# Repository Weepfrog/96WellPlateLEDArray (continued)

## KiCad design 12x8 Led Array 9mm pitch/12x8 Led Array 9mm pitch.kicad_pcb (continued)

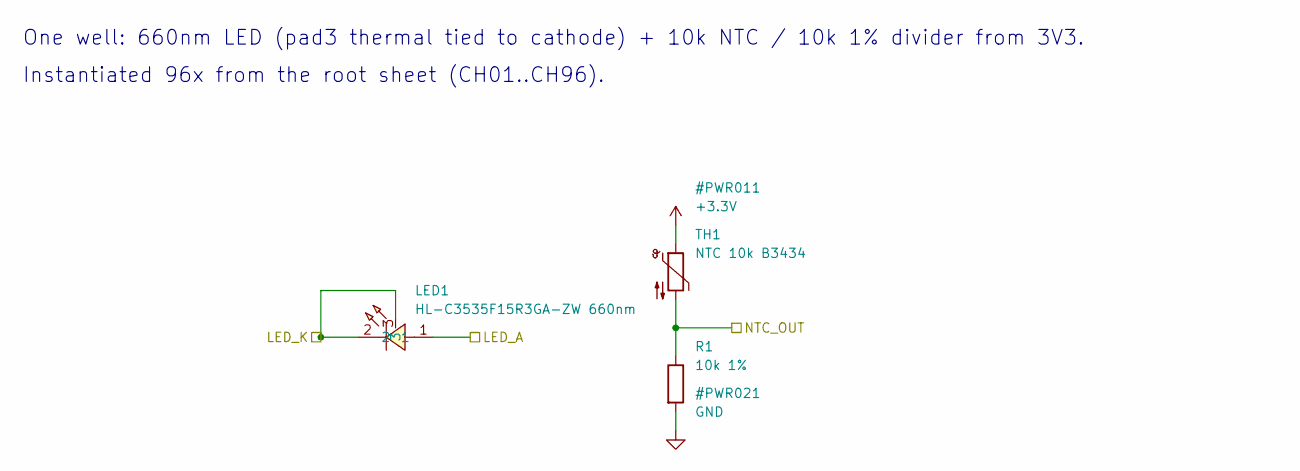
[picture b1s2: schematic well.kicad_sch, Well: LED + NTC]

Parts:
LED1: HL-C3535F15R3GA-ZW 660nm; LED-SMD_3P-L3.5-W3.5_NLW3535AV2; LCSC C5445086
R1: 10k 1%; R_0603_1608Metric; LCSC C25804
TH1: NTC 10k B3434; R_0603_1608Metric; LCSC C13564

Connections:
+3.3V: TH1.1; also elsewhere on the board
/LED_A14: LED1.1; also elsewhere on the board
/LED_K14: LED1.2, LED1.3; also elsewhere on the board
/NTC1: R1.1, TH1.2; also elsewhere on the board
GND: R1.2; also elsewhere on the board

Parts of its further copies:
LED2, LED3, LED4, LED5, LED6, LED7, LED8, LED9, LED10, LED11, LED12, LED13, LED14, LED15, LED16, LED17, LED18, LED19, LED20, LED21, LED22, LED23, LED24, LED25, LED26, LED27, LED28, LED29, LED30, LED31, LED32, LED33, LED34, LED35, LED36, LED37, LED38, LED39, LED40, LED41, LED42, LED43, LED44, LED45, LED46, LED47, LED48, LED49, LED50, LED51, LED52, LED53, LED54, LED55, LED56, LED57, LED58, LED59, LED60, LED61, LED62, LED63, LED64, LED65, LED66, LED67, LED68, LED69, LED70, LED71, LED72, LED73, LED74, LED75, LED76, LED77, LED78, LED79, LED80, LED81, LED82, LED83, LED84, LED85, LED86, LED87, LED88, LED89, LED90, LED91, LED92, LED93, LED94, LED95, LED96: HL-C3535F15R3GA-ZW 660nm; LED-SMD_3P-L3.5-W3.5_NLW3535AV2; LCSC C5445086
R2, R3, R4, R5, R6, R7, R8, R9, R10, R11, R12, R13, R14, R15, R16, R17, R18, R19, R20, R21, R22, R23, R24, R25, R26, R27, R28, R29, R30, R31, R32, R33, R34, R35, R36, R37, R38, R39, R40, R41, R42, R43, R44, R45, R46, R47, R48, R49, R50, R51, R52, R53, R54, R55, R56, R57, R58, R59, R60, R61, R62, R63, R64, R65, R66, R67, R68, R69, R70, R71, R72, R73, R74, R75, R76, R77, R78, R79, R80, R81, R82, R83, R84, R85, R86, R87, R88, R89, R90, R91, R92, R93, R94, R95, R96: 10k 1%; R_0603_1608Metric; LCSC C25804
TH2, TH3, TH4, TH5, TH6, TH7, TH8, TH9, TH10, TH11, TH12, TH13, TH14, TH15, TH16, TH17, TH18, TH19, TH20, TH21, TH22, TH23, TH24, TH25, TH26, TH27, TH28, TH29, TH30, TH31, TH32, TH33, TH34, TH35, TH36, TH37, TH38, TH39, TH40, TH41, TH42, TH43, TH44, TH45, TH46, TH47, TH48, TH49, TH50, TH51, TH52, TH53, TH54, TH55, TH56, TH57, TH58, TH59, TH60, TH61, TH62, TH63, TH64, TH65, TH66, TH67, TH68, TH69, TH70, TH71, TH72, TH73, TH74, TH75, TH76, TH77, TH78, TH79, TH80, TH81, TH82, TH83, TH84, TH85, TH86, TH87, TH88, TH89, TH90, TH91, TH92, TH93, TH94, TH95, TH96: NTC 10k B3434; R_0603_1608Metric; LCSC C13564

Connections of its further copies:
+3.3V: TH2.1, TH3.1, TH4.1, TH5.1, TH6.1, TH7.1, TH8.1, TH9.1, TH10.1, TH11.1, TH12.1, TH13.1, TH14.1, TH15.1, TH16.1, TH17.1, TH18.1, TH19.1, TH20.1, TH21.1, TH22.1, TH23.1, TH24.1, TH25.1, TH26.1, TH27.1, TH28.1, TH29.1, TH30.1, TH31.1, TH32.1, TH33.1, TH34.1, TH35.1, TH36.1, TH37.1, TH38.1, TH39.1, TH40.1, TH41.1, TH42.1, TH43.1, TH44.1, TH45.1, TH46.1, TH47.1, TH48.1, TH49.1, TH50.1, TH51.1, TH52.1, TH53.1, TH54.1, TH55.1, TH56.1, TH57.1, TH58.1, TH59.1, TH60.1, TH61.1, TH62.1, TH63.1, TH64.1, TH65.1, TH66.1, TH67.1, TH68.1, TH69.1, TH70.1, TH71.1, TH72.1, TH73.1, TH74.1, TH75.1, TH76.1, TH77.1, TH78.1, TH79.1, TH80.1, TH81.1, TH82.1, TH83.1, TH84.1, TH85.1, TH86.1, TH87.1, TH88.1, TH89.1, TH90.1, TH91.1, TH92.1, TH93.1, TH94.1, TH95.1, TH96.1; also elsewhere on the board
/LED_A1: LED37.1; also elsewhere on the board
/LED_A2: LED38.1; also elsewhere on the board
/LED_A3: LED39.1; also elsewhere on the board
/LED_A4: LED40.1; also elsewhere on the board
/LED_A5: LED25.1; also elsewhere on the board
/LED_A6: LED41.1; also elsewhere on the board
/LED_A7: LED26.1; also elsewhere on the board
/LED_A8: LED27.1; also elsewhere on the board
/LED_A9: LED13.1; also elsewhere on the board
/LED_A10: LED42.1; also elsewhere on the board
/LED_A11: LED28.1; also elsewhere on the board
/LED_A12: LED14.1; also elsewhere on the board
/LED_A13: LED15.1; also elsewhere on the board
/LED_A15: LED29.1; also elsewhere on the board
/LED_A16: LED2.1; also elsewhere on the board
/LED_A17: LED16.1; also elsewhere on the board
/LED_A18: LED3.1; also elsewhere on the board
/LED_A19: LED43.1; also elsewhere on the board
/LED_A20: LED17.1; also elsewhere on the board
/LED_A21: LED4.1; also elsewhere on the board
/LED_A22: LED30.1; also elsewhere on the board
/LED_A23: LED31.1; also elsewhere on the board
/LED_A24: LED18.1; also elsewhere on the board
/LED_A25: LED5.1; also elsewhere on the board
/LED_A26: LED44.1; also elsewhere on the board
/LED_A27: LED32.1; also elsewhere on the board
/LED_A28: LED6.1; also elsewhere on the board
/LED_A29: LED19.1; also elsewhere on the board
/LED_A30: LED45.1; also elsewhere on the board
/LED_A31: LED7.1; also elsewhere on the board
/LED_A32: LED20.1; also elsewhere on the board
/LED_A33: LED8.1; also elsewhere on the board
/LED_A34: LED33.1; also elsewhere on the board
/LED_A35: LED21.1; also elsewhere on the board
/LED_A36: LED9.1; also elsewhere on the board
/LED_A37: LED46.1; also elsewhere on the board
/LED_A38: LED34.1; also elsewhere on the board
/LED_A39: LED22.1; also elsewhere on the board
/LED_A40: LED10.1; also elsewhere on the board
/LED_A41: LED47.1; also elsewhere on the board
/LED_A42: LED35.1; also elsewhere on the board
/LED_A43: LED23.1; also elsewhere on the board
/LED_A44: LED11.1; also elsewhere on the board
/LED_A45: LED48.1; also elsewhere on the board
/LED_A46: LED36.1; also elsewhere on the board
/LED_A47: LED24.1; also elsewhere on the board
/LED_A48: LED12.1; also elsewhere on the board
/LED_A49: LED65.1; also elsewhere on the board
/LED_A50: LED86.1; also elsewhere on the board
/LED_A51: LED75.1; also elsewhere on the board
/LED_A52: LED85.1; also elsewhere on the board
/LED_A53: LED54.1; also elsewhere on the board
/LED_A54: LED64.1; also elsewhere on the board
/LED_A55: LED74.1; also elsewhere on the board
/LED_A56: LED53.1; also elsewhere on the board
/LED_A57: LED73.1; also elsewhere on the board
/LED_A58: LED63.1; also elsewhere on the board
/LED_A59: LED62.1; also elsewhere on the board
/LED_A60: LED52.1; also elsewhere on the board
/LED_A61: LED61.1; also elsewhere on the board
/LED_A62: LED51.1; also elsewhere on the board
/LED_A63: LED50.1; also elsewhere on the board
/LED_A64: LED49.1; also elsewhere on the board
/LED_A65: LED87.1; also elsewhere on the board
/LED_A66: LED76.1; also elsewhere on the board
/LED_A67: LED55.1; also elsewhere on the board
/LED_A68: LED88.1; also elsewhere on the board
/LED_A69: LED66.1; also elsewhere on the board
/LED_A70: LED77.1; also elsewhere on the board
/LED_A71: LED56.1; also elsewhere on the board
/LED_A72: LED78.1; also elsewhere on the board
/LED_A73: LED89.1; also elsewhere on the board
/LED_A74: LED67.1; also elsewhere on the board
/LED_A75: LED90.1; also elsewhere on the board
/LED_A76: LED79.1; also elsewhere on the board
/LED_A77: LED68.1; also elsewhere on the board
/LED_A78: LED57.1; also elsewhere on the board
/LED_A79: LED91.1; also elsewhere on the board
/LED_A80: LED80.1; also elsewhere on the board
/LED_A81: LED92.1; also elsewhere on the board
/LED_A82: LED69.1; also elsewhere on the board
/LED_A83: LED81.1; also elsewhere on the board
/LED_A84: LED93.1; also elsewhere on the board
/LED_A85: LED58.1; also elsewhere on the board
/LED_A86: LED70.1; also elsewhere on the board
/LED_A87: LED82.1; also elsewhere on the board
/LED_A88: LED94.1; also elsewhere on the board
/LED_A89: LED59.1; also elsewhere on the board
/LED_A90: LED71.1; also elsewhere on the board
/LED_A91: LED83.1; also elsewhere on the board
/LED_A92: LED95.1; also elsewhere on the board
/LED_A93: LED60.1; also elsewhere on the board
/LED_A94: LED72.1; also elsewhere on the board
/LED_A95: LED84.1; also elsewhere on the board
/LED_A96: LED96.1; also elsewhere on the board
/LED_K1: LED37.2, LED37.3; also elsewhere on the board
/LED_K2: LED38.2, LED38.3; also elsewhere on the board
/LED_K3: LED39.2, LED39.3; also elsewhere on the board
/LED_K4: LED40.2, LED40.3; also elsewhere on the board
/LED_K5: LED25.2, LED25.3; also elsewhere on the board
/LED_K6: LED41.2, LED41.3; also elsewhere on the board
/LED_K7: LED26.2, LED26.3; also elsewhere on the board
/LED_K8: LED27.2, LED27.3; also elsewhere on the board
/LED_K9: LED13.2, LED13.3; also elsewhere on the board
/LED_K10: LED42.2, LED42.3; also elsewhere on the board
/LED_K11: LED28.2, LED28.3; also elsewhere on the board
/LED_K12: LED14.2, LED14.3; also elsewhere on the board
/LED_K13: LED15.2, LED15.3; also elsewhere on the board
/LED_K15: LED29.2, LED29.3; also elsewhere on the board
/LED_K16: LED2.2, LED2.3; also elsewhere on the board
/LED_K17: LED16.2, LED16.3; also elsewhere on the board
/LED_K18: LED3.2, LED3.3; also elsewhere on the board
/LED_K19: LED43.2, LED43.3; also elsewhere on the board
/LED_K20: LED17.2, LED17.3; also elsewhere on the board
/LED_K21: LED4.2, LED4.3; also elsewhere on the board
/LED_K22: LED30.2, LED30.3; also elsewhere on the board
/LED_K23: LED31.2, LED31.3; also elsewhere on the board
/LED_K24: LED18.2, LED18.3; also elsewhere on the board
/LED_K25: LED5.2, LED5.3; also elsewhere on the board
/LED_K26: LED44.2, LED44.3; also elsewhere on the board
/LED_K27: LED32.2, LED32.3; also elsewhere on the board
/LED_K28: LED6.2, LED6.3; also elsewhere on the board
/LED_K29: LED19.2, LED19.3; also elsewhere on the board
/LED_K30: LED45.2, LED45.3; also elsewhere on the board
/LED_K31: LED7.2, LED7.3; also elsewhere on the board
/LED_K32: LED20.2, LED20.3; also elsewhere on the board
/LED_K33: LED8.2, LED8.3; also elsewhere on the board
/LED_K34: LED33.2, LED33.3; also elsewhere on the board
/LED_K35: LED21.2, LED21.3; also elsewhere on the board
/LED_K36: LED9.2, LED9.3; also elsewhere on the board
/LED_K37: LED46.2, LED46.3; also elsewhere on the board
/LED_K38: LED34.2, LED34.3; also elsewhere on the board
/LED_K39: LED22.2, LED22.3; also elsewhere on the board
/LED_K40: LED10.2, LED10.3; also elsewhere on the board
/LED_K41: LED47.2, LED47.3; also elsewhere on the board
/LED_K42: LED35.2, LED35.3; also elsewhere on the board
/LED_K43: LED23.2, LED23.3; also elsewhere on the board
/LED_K44: LED11.2, LED11.3; also elsewhere on the board
/LED_K45: LED48.2, LED48.3; also elsewhere on the board
/LED_K46: LED36.2, LED36.3; also elsewhere on the board
/LED_K47: LED24.2, LED24.3; also elsewhere on the board
/LED_K48: LED12.2, LED12.3; also elsewhere on the board
/LED_K49: LED65.2, LED65.3; also elsewhere on the board
/LED_K50: LED86.2, LED86.3; also elsewhere on the board
/LED_K51: LED75.2, LED75.3; also elsewhere on the board
/LED_K52: LED85.2, LED85.3; also elsewhere on the board
/LED_K53: LED54.2, LED54.3; also elsewhere on the board
/LED_K54: LED64.2, LED64.3; also elsewhere on the board
/LED_K55: LED74.2, LED74.3; also elsewhere on the board
/LED_K56: LED53.2, LED53.3; also elsewhere on the board
/LED_K57: LED73.2, LED73.3; also elsewhere on the board
/LED_K58: LED63.2, LED63.3; also elsewhere on the board
/LED_K59: LED62.2, LED62.3; also elsewhere on the board
/LED_K60: LED52.2, LED52.3; also elsewhere on the board
/LED_K61: LED61.2, LED61.3; also elsewhere on the board
/LED_K62: LED51.2, LED51.3; also elsewhere on the board
/LED_K63: LED50.2, LED50.3; also elsewhere on the board
/LED_K64: LED49.2, LED49.3; also elsewhere on the board
/LED_K65: LED87.2, LED87.3; also elsewhere on the board
/LED_K66: LED76.2, LED76.3; also elsewhere on the board
/LED_K67: LED55.2, LED55.3; also elsewhere on the board
/LED_K68: LED88.2, LED88.3; also elsewhere on the board
/LED_K69: LED66.2, LED66.3; also elsewhere on the board
/LED_K70: LED77.2, LED77.3; also elsewhere on the board
/LED_K71: LED56.2, LED56.3; also elsewhere on the board
/LED_K72: LED78.2, LED78.3; also elsewhere on the board
/LED_K73: LED89.2, LED89.3; also elsewhere on the board
/LED_K74: LED67.2, LED67.3; also elsewhere on the board
/LED_K75: LED90.2, LED90.3; also elsewhere on the board
/LED_K76: LED79.2, LED79.3; also elsewhere on the board
/LED_K77: LED68.2, LED68.3; also elsewhere on the board
/LED_K78: LED57.2, LED57.3; also elsewhere on the board
/LED_K79: LED91.2, LED91.3; also elsewhere on the board
/LED_K80: LED80.2, LED80.3; also elsewhere on the board
/LED_K81: LED92.2, LED92.3; also elsewhere on the board
/LED_K82: LED69.2, LED69.3; also elsewhere on the board
/LED_K83: LED81.2, LED81.3; also elsewhere on the board
/LED_K84: LED93.2, LED93.3; also elsewhere on the board
/LED_K85: LED58.2, LED58.3; also elsewhere on the board
/LED_K86: LED70.2, LED70.3; also elsewhere on the board
/LED_K87: LED82.2, LED82.3; also elsewhere on the board
/LED_K88: LED94.2, LED94.3; also elsewhere on the board
/LED_K89: LED59.2, LED59.3; also elsewhere on the board
/LED_K90: LED71.2, LED71.3; also elsewhere on the board
/LED_K91: LED83.2, LED83.3; also elsewhere on the board
/LED_K92: LED95.2, LED95.3; also elsewhere on the board
/LED_K93: LED60.2, LED60.3; also elsewhere on the board
/LED_K94: LED72.2, LED72.3; also elsewhere on the board
/LED_K95: LED84.2, LED84.3; also elsewhere on the board
/LED_K96: LED96.2, LED96.3; also elsewhere on the board
/NTC2: R2.1, TH2.2; also elsewhere on the board
/NTC3: R3.1, TH3.2; also elsewhere on the board
/NTC4: R4.1, TH4.2; also elsewhere on the board
/NTC5: R5.1, TH5.2; also elsewhere on the board
/NTC6: R6.1, TH6.2; also elsewhere on the board
/NTC7: R7.1, TH7.2; also elsewhere on the board
/NTC8: R8.1, TH8.2; also elsewhere on the board
/NTC9: R9.1, TH9.2; also elsewhere on the board
/NTC10: R10.1, TH10.2; also elsewhere on the board
/NTC11: R11.1, TH11.2; also elsewhere on the board
/NTC12: R12.1, TH12.2; also elsewhere on the board
/NTC13: R13.1, TH13.2; also elsewhere on the board
/NTC14: R14.1, TH14.2; also elsewhere on the board
/NTC15: R15.1, TH15.2; also elsewhere on the board
/NTC16: R16.1, TH16.2; also elsewhere on the board
/NTC17: R17.1, TH17.2; also elsewhere on the board
/NTC18: R18.1, TH18.2; also elsewhere on the board
/NTC19: R19.1, TH19.2; also elsewhere on the board
/NTC20: R20.1, TH20.2; also elsewhere on the board
/NTC21: R21.1, TH21.2; also elsewhere on the board
/NTC22: R22.1, TH22.2; also elsewhere on the board
/NTC23: R23.1, TH23.2; also elsewhere on the board
/NTC24: R24.1, TH24.2; also elsewhere on the board
/NTC25: R25.1, TH25.2; also elsewhere on the board
/NTC26: R26.1, TH26.2; also elsewhere on the board
/NTC27: R27.1, TH27.2; also elsewhere on the board
/NTC28: R28.1, TH28.2; also elsewhere on the board
/NTC29: R29.1, TH29.2; also elsewhere on the board
/NTC30: R30.1, TH30.2; also elsewhere on the board
/NTC31: R31.1, TH31.2; also elsewhere on the board
/NTC32: R32.1, TH32.2; also elsewhere on the board
/NTC33: R33.1, TH33.2; also elsewhere on the board
/NTC34: R34.1, TH34.2; also elsewhere on the board
/NTC35: R35.1, TH35.2; also elsewhere on the board
/NTC36: R36.1, TH36.2; also elsewhere on the board
/NTC37: R37.1, TH37.2; also elsewhere on the board
/NTC38: R38.1, TH38.2; also elsewhere on the board
/NTC39: R39.1, TH39.2; also elsewhere on the board
/NTC40: R40.1, TH40.2; also elsewhere on the board
/NTC41: R41.1, TH41.2; also elsewhere on the board
/NTC42: R42.1, TH42.2; also elsewhere on the board
/NTC43: R43.1, TH43.2; also elsewhere on the board
/NTC44: R44.1, TH44.2; also elsewhere on the board
/NTC45: R45.1, TH45.2; also elsewhere on the board
/NTC46: R46.1, TH46.2; also elsewhere on the board
/NTC47: R47.1, TH47.2; also elsewhere on the board
/NTC48: R48.1, TH48.2; also elsewhere on the board
/NTC49: R49.1, TH49.2; also elsewhere on the board
/NTC50: R50.1, TH50.2; also elsewhere on the board
/NTC51: R51.1, TH51.2; also elsewhere on the board
/NTC52: R52.1, TH52.2; also elsewhere on the board
/NTC53: R53.1, TH53.2; also elsewhere on the board
/NTC54: R54.1, TH54.2; also elsewhere on the board
/NTC55: R55.1, TH55.2; also elsewhere on the board
/NTC56: R56.1, TH56.2; also elsewhere on the board
/NTC57: R57.1, TH57.2; also elsewhere on the board
/NTC58: R58.1, TH58.2; also elsewhere on the board
/NTC59: R59.1, TH59.2; also elsewhere on the board
/NTC60: R60.1, TH60.2; also elsewhere on the board
/NTC61: R61.1, TH61.2; also elsewhere on the board
/NTC62: R62.1, TH62.2; also elsewhere on the board
/NTC63: R63.1, TH63.2; also elsewhere on the board
/NTC64: R64.1, TH64.2; also elsewhere on the board
/NTC65: R65.1, TH65.2; also elsewhere on the board
/NTC66: R66.1, TH66.2; also elsewhere on the board
/NTC67: R67.1, TH67.2; also elsewhere on the board
/NTC68: R68.1, TH68.2; also elsewhere on the board
/NTC69: R69.1, TH69.2; also elsewhere on the board
/NTC70: R70.1, TH70.2; also elsewhere on the board
/NTC71: R71.1, TH71.2; also elsewhere on the board
/NTC72: R72.1, TH72.2; also elsewhere on the board
/NTC73: R73.1, TH73.2; also elsewhere on the board
/NTC74: R74.1, TH74.2; also elsewhere on the board
/NTC75: R75.1, TH75.2; also elsewhere on the board
/NTC76: R76.1, TH76.2; also elsewhere on the board
/NTC77: R77.1, TH77.2; also elsewhere on the board
/NTC78: R78.1, TH78.2; also elsewhere on the board
/NTC79: R79.1, TH79.2; also elsewhere on the board
/NTC80: R80.1, TH80.2; also elsewhere on the board
/NTC81: R81.1, TH81.2; also elsewhere on the board
/NTC82: R82.1, TH82.2; also elsewhere on the board
/NTC83: R83.1, TH83.2; also elsewhere on the board
/NTC84: R84.1, TH84.2; also elsewhere on the board
/NTC85: R85.1, TH85.2; also elsewhere on the board
/NTC86: R86.1, TH86.2; also elsewhere on the board
/NTC87: R87.1, TH87.2; also elsewhere on the board
/NTC88: R88.1, TH88.2; also elsewhere on the board
/NTC89: R89.1, TH89.2; also elsewhere on the board
/NTC90: R90.1, TH90.2; also elsewhere on the board
/NTC91: R91.1, TH91.2; also elsewhere on the board
/NTC92: R92.1, TH92.2; also elsewhere on the board
/NTC93: R93.1, TH93.2; also elsewhere on the board
/NTC94: R94.1, TH94.2; also elsewhere on the board
/NTC95: R95.1, TH95.2; also elsewhere on the board
/NTC96: R96.1, TH96.2; also elsewhere on the board
GND: R2.2, R3.2, R4.2, R5.2, R6.2, R7.2, R8.2, R9.2, R10.2, R11.2, R12.2, R13.2, R14.2, R15.2, R16.2, R17.2, R18.2, R19.2, R20.2, R21.2, R22.2, R23.2, R24.2, R25.2, R26.2, R27.2, R28.2, R29.2, R30.2, R31.2, R32.2, R33.2, R34.2, R35.2, R36.2, R37.2, R38.2, R39.2, R40.2, R41.2, R42.2, R43.2, R44.2, R45.2, R46.2, R47.2, R48.2, R49.2, R50.2, R51.2, R52.2, R53.2, R54.2, R55.2, R56.2, R57.2, R58.2, R59.2, R60.2, R61.2, R62.2, R63.2, R64.2, R65.2, R66.2, R67.2, R68.2, R69.2, R70.2, R71.2, R72.2, R73.2, R74.2, R75.2, R76.2, R77.2, R78.2, R79.2, R80.2, R81.2, R82.2, R83.2, R84.2, R85.2, R86.2, R87.2, R88.2, R89.2, R90.2, R91.2, R92.2, R93.2, R94.2, R95.2, R96.2; also elsewhere on the board

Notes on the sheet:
One well: 660nm LED (pad3 thermal tied to cathode) + 10k NTC / 10k 1% divider from 3V3.
Instantiated 96x from the root sheet (CH01..CH96).

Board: 4 copper layers, 315 parts (0 on the bottom side), 300 nets, no tracks yet.

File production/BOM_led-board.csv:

Comment,Designator,Footprint,LCSC
NTC 10k B3434,"TH1,TH10,TH11,TH12,TH13,TH14,TH15,TH16,TH17,TH18,TH19,TH2,TH20,TH21,TH22,TH23,TH24,TH25,TH26,TH27,TH28,TH29,TH3,TH30,TH31,TH32,TH33,TH34,TH35,TH36,TH37,TH38,TH39,TH4,TH40,TH41,TH42,TH43,TH44,TH45,TH46,TH47,TH48,TH49,TH5,TH50,TH51,TH52,TH53,TH54,TH55,TH56,TH57,TH58,TH59,TH6,TH60,TH61,TH62,TH63,TH64,TH65,TH66,TH67,TH68,TH69,TH7,TH70,TH71,TH72,TH73,TH74,TH75,TH76,TH77,TH78,TH79,TH8,TH80,TH81,TH82,TH83,TH84,TH85,TH86,TH87,TH88,TH89,TH9,TH90,TH91,TH92,TH93,TH94,TH95,TH96",R_0603_1608Metric,C13564
100nF,"C1,C2,C3,C4,C5,C6",C_0603_1608Metric,C14663
10k 1%,"R1,R10,R11,R12,R13,R14,R15,R16,R17,R18,R19,R2,R20,R21,R22,R23,R24,R25,R26,R27,R28,R29,R3,R30,R31,R32,R33,R34,R35,R36,R37,R38,R39,R4,R40,R41,R42,R43,R44,R45,R46,R47,R48,R49,R5,R50,R51,R52,R53,R54,R55,R56,R57,R58,R59,R6,R60,R61,R62,R63,R64,R65,R66,R67,R68,R69,R7,R70,R71,R72,R73,R74,R75,R76,R77,R78,R79,R8,R80,R81,R82,R83,R84,R85,R86,R87,R88,R89,R9,R90,R91,R92,R93,R94,R95,R96",R_0603_1608Metric,C25804
CD74HC4067M96,"U1,U2,U3,U4,U5,U6",SOIC-24_L15.4-W7.5-P1.27-LS10.3-BL,C496123
HL-C3535F15R3GA-ZW 660nm,"LED1,LED10,LED11,LED12,LED13,LED14,LED15,LED16,LED17,LED18,LED19,LED2,LED20,LED21,LED22,LED23,LED24,LED25,LED26,LED27,LED28,LED29,LED3,LED30,LED31,LED32,LED33,LED34,LED35,LED36,LED37,LED38,LED39,LED4,LED40,LED41,LED42,LED43,LED44,LED45,LED46,LED47,LED48,LED49,LED5,LED50,LED51,LED52,LED53,LED54,LED55,LED56,LED57,LED58,LED59,LED6,LED60,LED61,LED62,LED63,LED64,LED65,LED66,LED67,LED68,LED69,LED7,LED70,LED71,LED72,LED73,LED74,LED75,LED76,LED77,LED78,LED79,LED8,LED80,LED81,LED82,LED83,LED84,LED85,LED86,LED87,LED88,LED89,LED9,LED90,LED91,LED92,LED93,LED94,LED95,LED96",LED-SMD_3P-L3.5-W3.5_NLW3535AV2,C5445086
